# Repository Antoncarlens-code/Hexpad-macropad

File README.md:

# Hexpad — a hex-shaped 6-key macropad

A 6-key (3×2) macropad with a rotary encoder: 3D-printed case, custom 2-layer PCB,
and KMK firmware, driven by a **Seeed XIAO RP2040**. Keys wire **direct to GPIO**
(no matrix, no diodes), and the encoder handles volume/scroll.

<!-- HACKPAD: a full render showing ALL parts is required. Export one from the
     KiCad 3D viewer or your CAD tool and drop it at the path below. -->

## Inspiration & challenges

I wanted a compact editing/clipboard pad with a volume knob that didn't look like
every other square macropad — so Hexpad uses a hexagonal silhouette around a
centered 3×2 key cluster with the encoder up top.

Two things were genuinely fiddly. First, the original top-plate CAD came out of an
early IDE session malformed — the plate solid was fused to a stray slab 74 mm
below it, so it "levitated" in the slicer. I had to reverse-engineer the real
dimensions from the STEP geometry and rebuild the plate as a clean parametric
build123d script. Second, rather than hand-draw the board I generated the PCB
programmatically with KiCad's `pcbnew` API from a single coordinate spec, which
guarantees the switch, encoder, and mounting-hole positions line up exactly with
the printed plate (19.05 mm pitch, mounts at ±32 × ±31 mm).

## Gallery

| Schematic | PCB | Case |
|-----------|-----|------|
|  |  |  |

<!-- HACKPAD requires a photo of each: the schematic, the PCB (KiCad render or the
     real board), and the case. Add the three images to docs/images/. -->

## Bill of materials

Full sheet: [`docs/electronics/hexpad-bom.csv`](docs/electronics/hexpad-bom.csv).

| Qty | Part | Notes |
|-----|------|-------|
| 1 | Seeed XIAO RP2040 | MCU, mounted on the back; USB-C exits the front edge |
| 6 | Cherry MX (or compatible) switch | `MX_Only_1.00u`, direct-wired, one GPIO each |
| 1 | Alps EC11 rotary encoder w/ switch | A/B + push → 3 GPIO, common → GND |
| 4 | M2 screw (~6 mm) | through the case into the plate's corner posts |
| 6 / 1 | MX keycaps / encoder knob | cosmetic |
| 0 | diodes | **none** — direct wiring is valid for ≤7 keys |

## Project layout

| Folder | Contents |
|--------|----------|
| `cad/` | Enclosure: STEP blueprints + parametric build123d source |
| `pcb/` | KiCad 10 PCB project, schematic, + fabrication Gerbers |
| `firmware/` | KMK (CircuitPython) keymap |
| `docs/electronics/` | Schematic (SVG), BOM, PCB design notes |
| `docs/images/` | Render + schematic/PCB/case photos for this README |

## PCB

| File | Purpose |
|------|---------|
| `pcb/hexpad.kicad_sch` | Schematic (XIAO + 6 switches + encoder) |
| `pcb/hexpad.kicad_pcb` | KiCad 10 board, branded, routed |
| `pcb/hexpad-gerbers.zip` | **Upload to JLCPCB** to order boards |
| `pcb/build_hexpad_pcb.py` / `build_hexpad_sch.py` | Regenerate board/schematic from the spec |

2-layer, **76 × 74 mm** (within the 100 mm limit), silkscreen-branded "Hexpad",
matching the plate's switch / encoder / mounting coordinates.

## Firmware

KMK keymap at `firmware/code.py`. Default: front row Copy/Paste/Cut, rear row
Undo/Redo/Save, encoder = volume (press = mute). See `firmware/README.md` for
flashing and remapping.

## Pin map

| Input | XIAO pin | | Input | XIAO pin |
|-------|----------|-|-------|----------|
| SW1–SW3 (front) | D0, D1, D2 | | Encoder A / B | D8 / D9 |
| SW4–SW6 (rear) | D3, D6, D7 | | Encoder push | D10 |

`D4`/`D5` (SDA/SCL) left free for a future OLED. All inputs use the RP2040's
internal pull-ups.

## Toolchain

build123d (CAD → STEP) · KiCad 10 (PCB) · Bambu Studio (slicing) · CircuitPython + KMK.

## Submission checklist (Hackpad)

- [x] DRC: 0 errors, 0 unconnected (only silk + courtyard warnings) — re-plotted after branding
- [x] "Hexpad" on the PCB silkscreen
- [x] "Hexpad" engraved on the top plate (front margin, 0.6 mm deep) — **reprint the plate to get it physically**
- [ ] 3D-printed parts need no supports / tolerances ~0.25 mm *(verify on your physical print)*
- [x] PCB < 100 × 100 mm; ≤16 switches, ≤2 encoders, ≤1 OLED, ≤16 LEDs
- [x] README photos: render + PCB + schematic + case (`docs/images/`)

## Build checklist

- [x] CAD: top plate + bottom case
- [x] PCB: schematic + routed board + Gerbers
- [x] Firmware keymap
- [x] Re-plot Gerbers after the silkscreen branding change
- [ ] Order PCB from JLCPCB · print case · solder · flash · assemble

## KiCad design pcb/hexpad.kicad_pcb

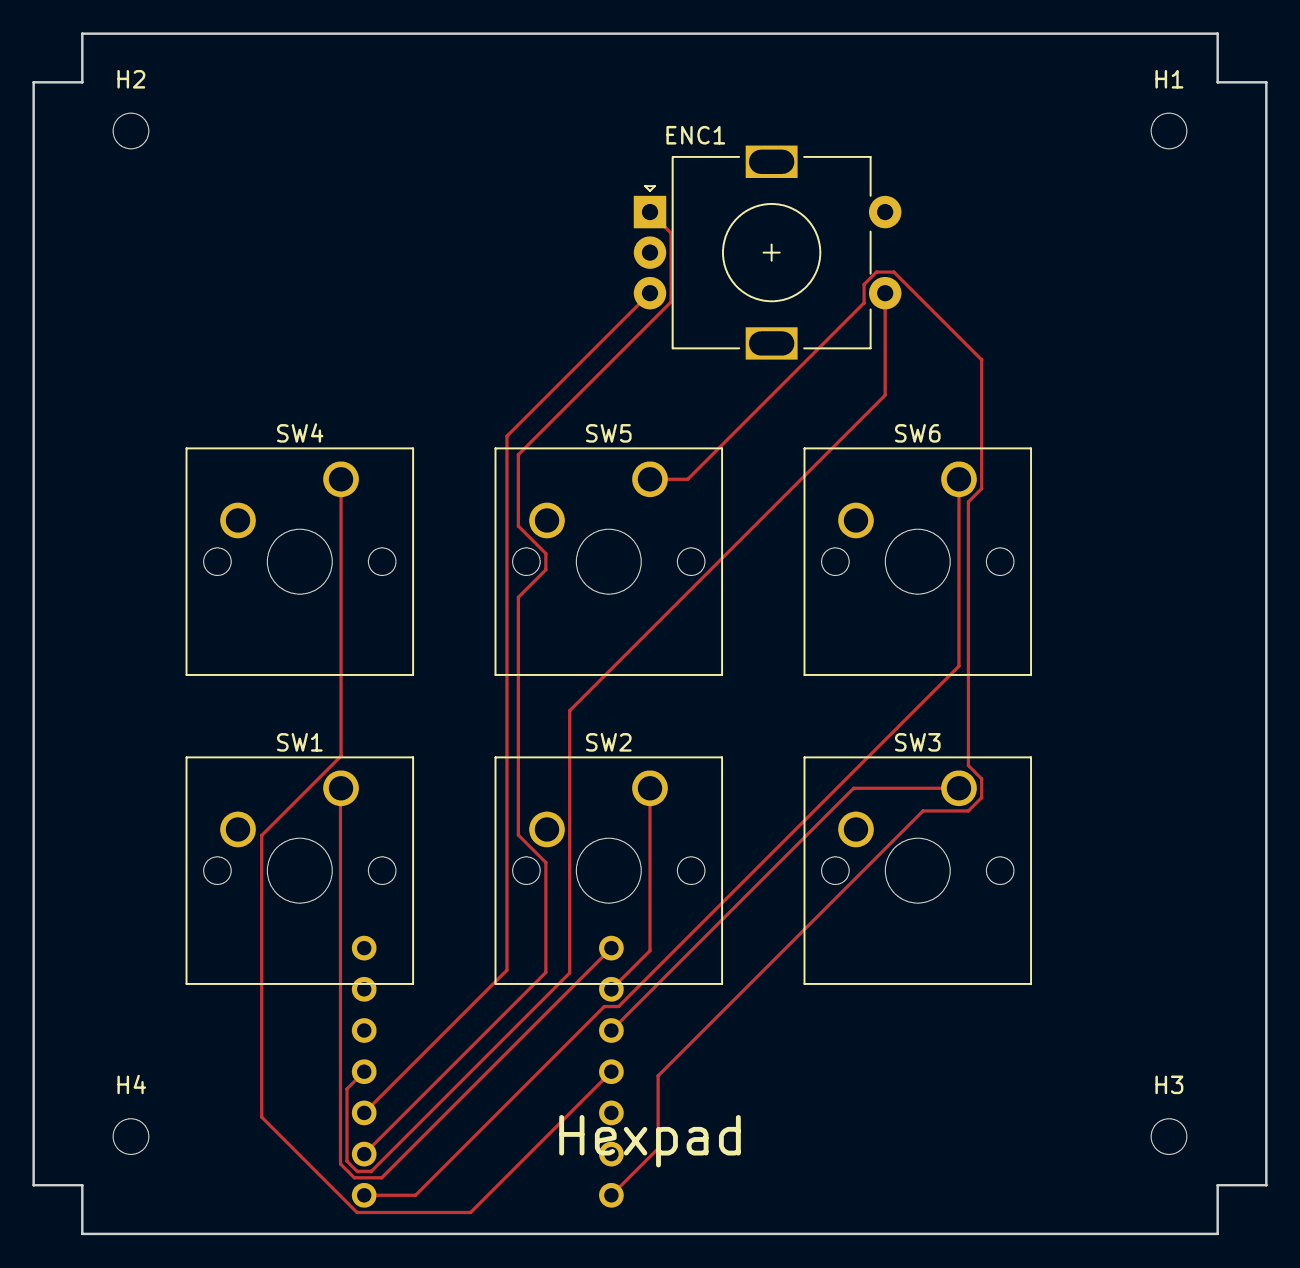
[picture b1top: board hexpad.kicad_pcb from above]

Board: 2 copper layers, 76.0 x 74.0 mm, 12 parts (1 on the bottom side), 10 nets.

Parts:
ENC1: EC11; RotaryEncoder_Alps_EC11E-Switch_Vertical_H20mm
H1, H2, H3, H4: M2; MountingHole_2.2mm_M2
SW1, SW2, SW3, SW4, SW5, SW6: SW_MX; SW_Cherry_MX_1.00u_PCB
U1: XIAO-RP2040

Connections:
ENCA: ENC1.A, U1.9
ENCB: ENC1.B, U1.10
ENCSW: ENC1.S1, U1.11
GND: ENC1.C, ENC1.MP, ENC1.S2, SW1.2, SW2.2, SW3.2, SW4.2, SW5.2, SW6.2, U1.13
SW1: SW1.1, U1.1
SW2: SW2.1, U1.2
SW3: SW3.1, U1.3
SW4: SW4.1, U1.4
SW5: SW5.1, U1.7
SW6: SW6.1, U1.8

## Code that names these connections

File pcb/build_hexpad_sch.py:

"""Generate hexpad.kicad_sch (schematic) matching the PCB's nets, via kiutils.

12 components: U1 (XIAO RP2040), SW1-6 (SW_Push), ENC1 (RotaryEncoder_Switch),
H1-4 (MountingHole), plus a PWR_FLAG on GND. Pins are connected with global
labels named after the board nets (SW1..SW6, ENCA, ENCB, ENCSW, GND); unused
XIAO pins get no-connects. Verify with: kicad-cli sch erc.

Run: python pcb/build_hexpad_sch.py
"""
import copy, os, uuid as uuidlib
from kiutils.schematic import Schematic
from kiutils.symbol import SymbolLib
from kiutils.items.schitems import SchematicSymbol, GlobalLabel, NoConnect, Connection
from kiutils.items.common import Position, Property, Effects, Font

SYM = r"C:/Program Files/KiCad/10.0/share/kicad/symbols"
OUT = os.path.join(os.path.dirname(os.path.abspath(__file__)), "hexpad.kicad_sch")
GRID = 1.27  # KiCad schematic connection grid (50 mil)

def U():
    return str(uuidlib.uuid4())

def g(v):  # snap to connection grid
    return round(v / GRID) * GRID

def load(libfile, name):
    lib = SymbolLib.from_file(os.path.join(SYM, libfile))
    for s in lib.symbols:
        if s.entryName == name:
            return copy.deepcopy(s)
    raise SystemExit(f"symbol not found: {name}")

# ---- XIAO symbol from a 14-pin connector, pins renamed ----
XIAO_PINS = {1:"D0",2:"D1",3:"D2",4:"D3",5:"D4",6:"D5",7:"D6",
             8:"D7",9:"D8",10:"D9",11:"D10",12:"3V3",13:"GND",14:"5V"}
xiao = load("Connector_Generic.kicad_sym", "Conn_01x14")
xiao.libId = "hexpad:XIAO-RP2040"
xiao.entryName = "XIAO-RP2040"
for u in xiao.units:
    for p in u.pins:
        p.name = XIAO_PINS[int(p.number)]
for pr in xiao.properties:
    if pr.key == "Value":
        pr.value = "XIAO-RP2040"
xiao_local = {int(p.number): (p.position.X, p.position.Y)
              for u in xiao.units for p in u.pins}

# standard symbols keep their real library nicknames (no "lib not configured" warning)
sw = load("Switch.kicad_sym", "SW_Push");                 sw.libId = "Switch:SW_Push"
enc = load("Device.kicad_sym", "RotaryEncoder_Switch");   enc.libId = "Device:RotaryEncoder_Switch"
mh = load("Mechanical.kicad_sym", "MountingHole");        mh.libId = "Mechanical:MountingHole"
pf = load("power.kicad_sym", "PWR_FLAG");                 pf.libId = "power:PWR_FLAG"

sch = Schematic.create_new()
sch.libSymbols = [xiao, sw, enc, mh, pf]

def eff():
    return Effects(font=Font(height=1.27, width=1.27))

def add_symbol(nick, entry, ref, value, x, y, angle=0):
    x, y = g(x), g(y)
    s = SchematicSymbol(libraryNickname=nick, entryName=entry,
                        position=Position(x, y, angle), unit=1, uuid=U())
    s.properties = [
        Property(key="Reference", value=ref, id=0, position=Position(x + 6.35, y - 2.54, 0), effects=eff()),
        Property(key="Value", value=value, id=1, position=Position(x + 6.35, y + 2.54, 0), effects=eff()),
    ]
    sch.schematicSymbols.append(s)
    return x, y

def label(net, x, y, angle=0):
    sch.globalLabels.append(
        GlobalLabel(text=net, shape="bidirectional", position=Position(x, y, angle), effects=eff()))

def noconn(x, y):
    sch.noConnects.append(NoConnect(position=Position(x, y)))

STUB = 5.08  # 200 mil wire stub so each label sits clear of its symbol

def wire(x1, y1, x2, y2):
    c = Connection(type="wire", points=[Position(g(x1), g(y1)), Position(g(x2), g(y2))])
    c.uuid = U()
    sch.graphicalItems.append(c)

def stub_label(net, ax, ay, angle):
    """Draw a short stub off the pin and put the global label at its far end."""
    dx = {0: STUB, 180: -STUB}.get(angle, 0)
    dy = {90: -STUB, 270: STUB}.get(angle, 0)
    ex, ey = ax + dx, ay + dy
    if dx or dy:
        wire(ax, ay, ex, ey)
    label(net, ex, ey, angle)

def apin(sx, sy, local):  # angle 0, no mirror: abs = (x+px, y-py)
    return (sx + local[0], sy - local[1])

# ---- XIAO (right) ----
ux, uy = add_symbol("hexpad", "XIAO-RP2040", "U1", "XIAO-RP2040", 190.5, 110.49)
xiao_net = {1:"SW1", 2:"SW2", 3:"SW3", 4:"SW4", 7:"SW5", 8:"SW6",
            9:"ENCA", 10:"ENCB", 11:"ENCSW", 13:"GND"}
xiao_nc = [5, 6, 12, 14]
for pn, loc in xiao_local.items():
    ax, ay = apin(ux, uy, loc)
    if pn in xiao_net:
        stub_label(xiao_net[pn], ax, ay, 180)
    elif pn in xiao_nc:
        noconn(ax, ay)

# ---- switches (left column): pin1 = signal, pin2 = GND ----
for i, net in enumerate(["SW1", "SW2", "SW3", "SW4", "SW5", "SW6"]):
    sx, sy = add_symbol("Switch", "SW_Push", f"SW{i+1}", "SW_Push", 60.96, 71.12 + i * 20.32)
    p1 = apin(sx, sy, (-5.08, 0)); stub_label(net, p1[0], p1[1], 180)
    p2 = apin(sx, sy, (5.08, 0));  stub_label("GND", p2[0], p2[1], 0)

# ---- encoder (top-left) ----
ex, ey = add_symbol("Device", "RotaryEncoder_Switch", "ENC1", "EC11", 111.76, 50.8)
for loc, net, ang in [((-7.62, 2.54), "ENCA", 180), ((-7.62, -2.54), "ENCB", 180),
                      ((-7.62, 0.0), "GND", 180), ((7.62, 2.54), "ENCSW", 0),
                      ((7.62, -2.54), "GND", 0)]:
    ax, ay = apin(ex, ey, loc); stub_label(net, ax, ay, ang)

# ---- PWR_FLAG on GND ----
px, py = add_symbol("power", "PWR_FLAG", "#FLG1", "PWR_FLAG", 190.5, 149.86)
fx, fy = apin(px, py, (0.0, 0.0)); stub_label("GND", fx, fy, 0)

# ---- mounting holes (no pins) ----
for i, (hx, hy) in enumerate([(241.3, 40.64), (241.3, 55.88), (241.3, 71.12), (241.3, 86.36)]):
    add_symbol("Mechanical", "MountingHole", f"H{i+1}", "MountingHole", hx, hy)

sch.to_file(OUT)

# project symbol library + table so the custom XIAO lib is "configured"
# (removes the last ERC "library not in configuration" warning)
PROJ = os.path.dirname(OUT)
xlib = SymbolLib()
xlib.filePath = os.path.join(PROJ, "hexpad.kicad_sym")
xiao_libcopy = copy.deepcopy(xiao)
xiao_libcopy.libId = "XIAO-RP2040"
xlib.symbols = [xiao_libcopy]
xlib.to_file(xlib.filePath)
with open(os.path.join(PROJ, "sym-lib-table"), "w") as f:
    f.write('(sym_lib_table\n  (version 7)\n'
            '  (lib (name "hexpad")(type "KiCad")'
            '(uri "${KIPRJMOD}/hexpad.kicad_sym")(options "")(descr "hexpad project symbols"))\n)\n')

print(f"wrote {OUT}: {len(sch.schematicSymbols)} symbols, "
      f"{len(sch.globalLabels)} labels, {len(sch.noConnects)} no-connects")

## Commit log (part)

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2026-06-03 Initial commit: hexpad macropad CAD blueprints + project structure
2026-06-03 Add firmware/ folder for keyboard firmware
2026-06-03 feat(cad): base top plate body with corner notches
2026-06-03 feat(cad): add corner mounting posts with M2 pilot holes
2026-06-03 feat(cad): add 6 stepped MX switch cutouts (14/16mm)
2026-06-03 feat(cad): add EC11 encoder hole at (0, 26)
2026-06-03 feat(cad): regenerate assembly from clean plate + existing case
2026-06-04 Add schematic, brand PCB + plate, Hackpad submission prep
    Schematic + custom XIAO symbol; silkscreen + plate branding; KMK keymap; BOM/docs; gitignore cleanup.
2026-06-04 schematic: add wire stubs so labels don't overlap symbols
2026-06-05 firmware: add first-power-on troubleshooting guide
2026-06-05 Add interactive web demo for Hexpad
2026-06-05 Add production folder (gerbers, case STEPs, firmware) + web demo
2026-06-06 fix: align mounting holes to bottom case (X 31 to 32); regenerate PCB + gerbers
